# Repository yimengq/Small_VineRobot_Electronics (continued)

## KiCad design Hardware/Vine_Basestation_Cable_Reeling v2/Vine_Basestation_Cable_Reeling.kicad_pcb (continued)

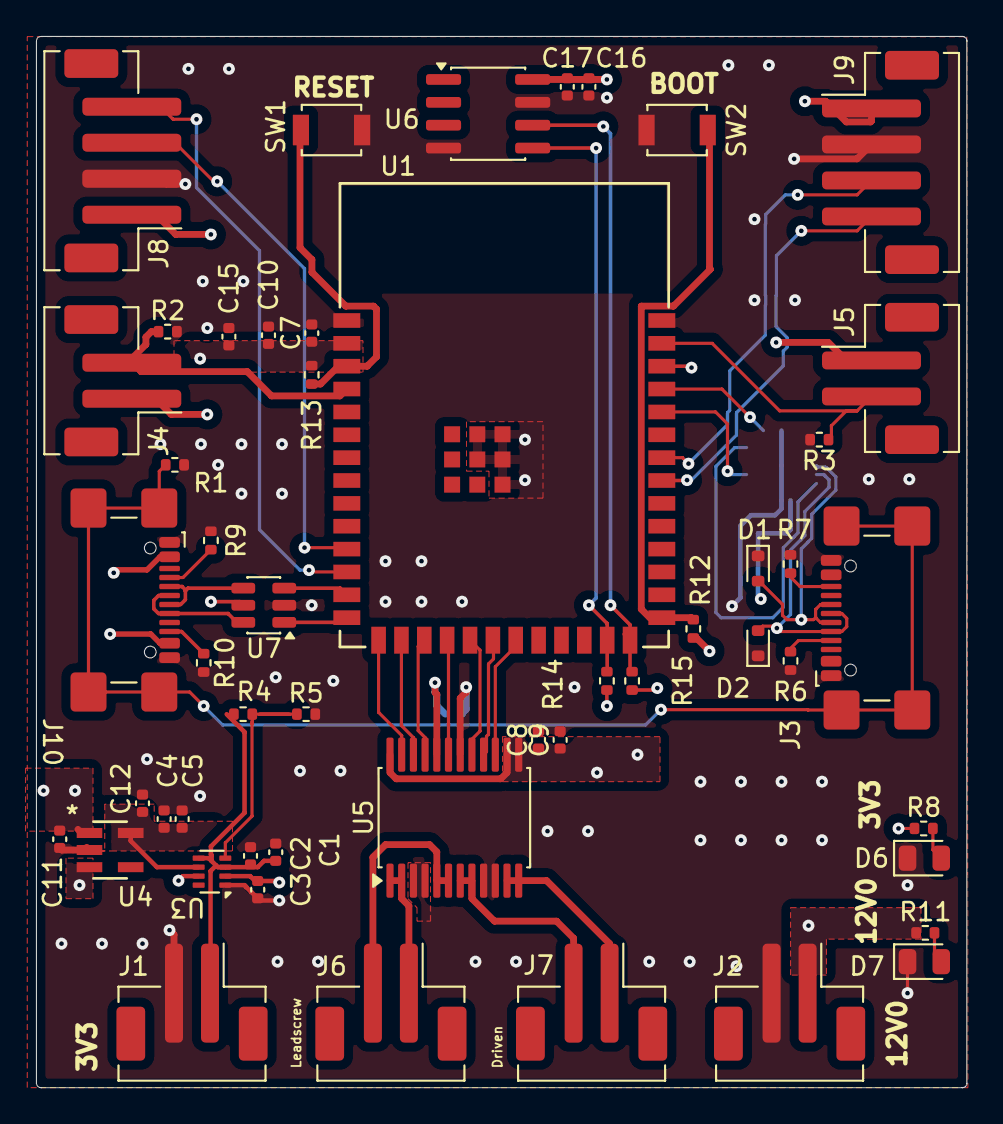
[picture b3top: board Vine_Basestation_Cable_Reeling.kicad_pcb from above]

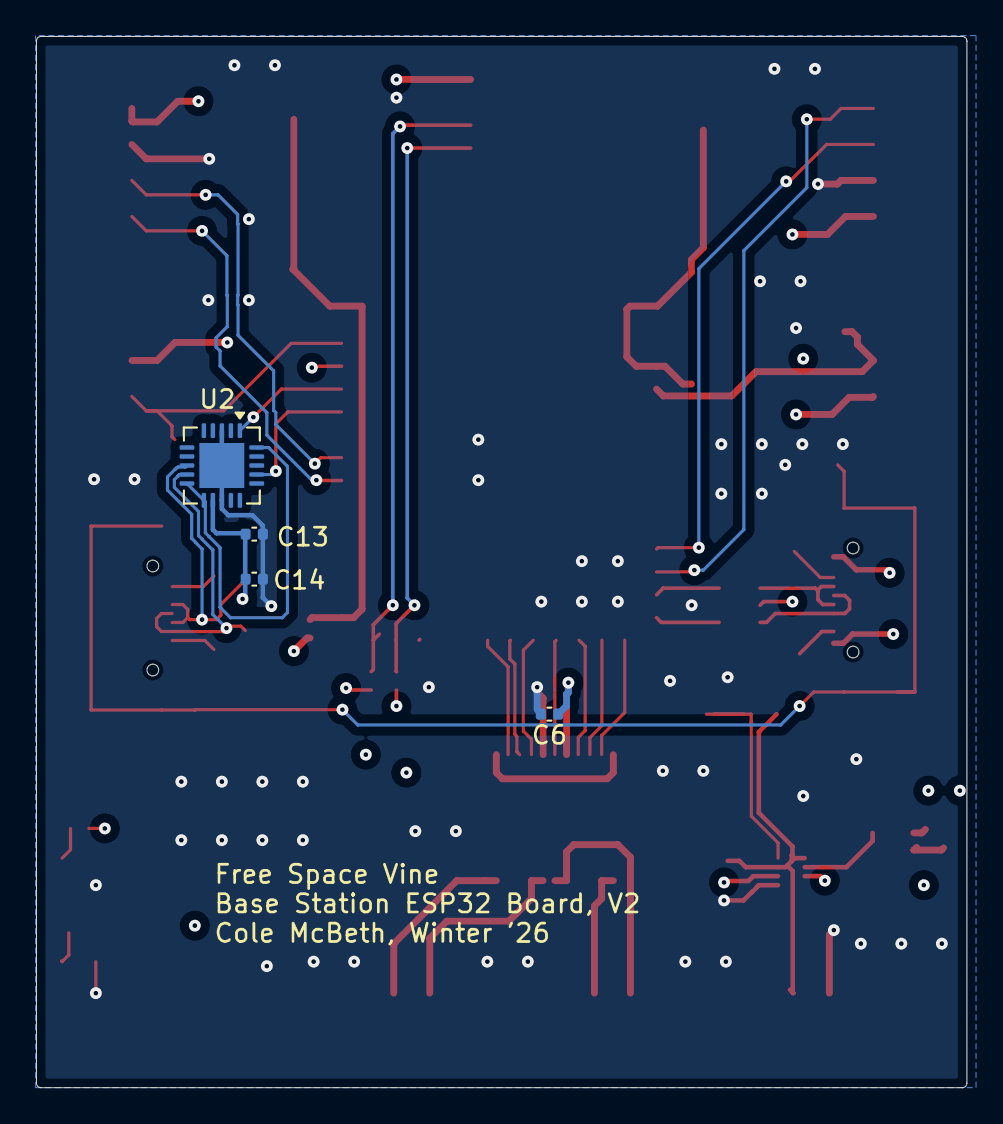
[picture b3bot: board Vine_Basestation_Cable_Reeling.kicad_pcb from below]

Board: 4 copper layers, 51.7 x 58.4 mm, 55 parts (4 on the bottom side), 44 nets.

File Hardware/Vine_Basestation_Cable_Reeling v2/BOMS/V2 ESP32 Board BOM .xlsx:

JLCPCB BOM Tool - BOM Matching
BOM name：ESP32 Board BOM - Vine_Basestation_Cable_Reeli-JLCPCB Assembly Order.x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 |  | Download Time：2025-10-29 07:45:15
PCB Assembled Qty：5 |  | Est. Total Price：39.0998
Designator | Comment | Footprint | JLCPCB Part #
C1,C5,C9,C14, C17 | 4.7u | Capacitor_SMD:C_0402_1005Metric | C23733
C2,C4,C7,C8,C11,C6,C13, C16 | 0.1u | Capacitor_SMD:C_0402_1005Metric | C1581
C3,C12,C15 | 1u | Capacitor_SMD:C_0402_1005Metric | C14445
C10 | 10u | Capacitor_SMD:C_0402_1005Metric | C15525
D1,D2,D3,D4 | D_TVS | Diode_SMD:D_SOD-523 | C20345394
D6,D7 | LED | LED_SMD:LED_0805_2012Metric | C84256
J1,J2,J4,J5,J6,J7 | Conn_01x02_Pin | Connector_JST:JST_PH_B2B-PH-SM4-TB_1x02-1MP_P2.00mm_Vertical | C265003
J3,J10 | USB_C_Receptacle_USB2.0_14P | Connector_USB:USB_C_Receptacle_GCT_USB4110 | C5143397
J8,J9 | Conn_01x04 | Connector_JST:JST_PH_B4B-PH-SM4-TB_1x04-1MP_P2.00mm_Vertical | C160354
J11 | Conn_02x12_Odd_Even | Connector_PinSocket_1.00mm:PinSocket_2x12_P1.00mm_Vertical_SMD | C22427765
R1 | 1M | Resistor_SMD:R_0402_1005Metric | C22369468
R2,R3,R4,R5,R12,R13 | 10k | Resistor_SMD:R_0402_1005Metric | C60489
R6,R7,R9,R10 | 5.1k | Resistor_SMD:R_0402_1005Metric | C105872
R8 | 270.0 | Resistor_SMD:R_0402_1005Metric | C25099
R11 | 2k | Resistor_SMD:R_0402_1005Metric | C4109
R14,R15 | 3.3k | Resistor_SMD:R_0402_1005Metric | C25890
SW1,SW2 | SW_Push | Button_Switch_SMD:SW_SPST_B3U-1000P | C231329
U1 | ESP32-S3-WROOM-1-N16R8 | ESP32-S3-WROOM-1-N16R8:ESP32-S3-WROOM-1_EXP | C2913202
U2 | FT231XQ | Package_DFN_QFN:QFN-20-1EP_4x4mm_P0.5mm_EP2.5x2.5mm | C132159
U3 | TPS2116DRL | Package_TO_SOT_SMD:SOT-583-8 | C3235557
U4 | TCR2EF33_LMCT | TCR2EF33_LM_CT:SOT-25SMV_TOS | C843273
U5 | TB6612FNG | Package_SO:SSOP-24_5.3x8.2mm_P0.65mm | C141517
U7 | USBLC6-2SC6 | Package_TO_SOT_SMD:SOT-23-6 | C7519
U6 | FM24CL16B | Package_SO:SOIC-8_3.9x4.9mm_P1.27mm | C2953561

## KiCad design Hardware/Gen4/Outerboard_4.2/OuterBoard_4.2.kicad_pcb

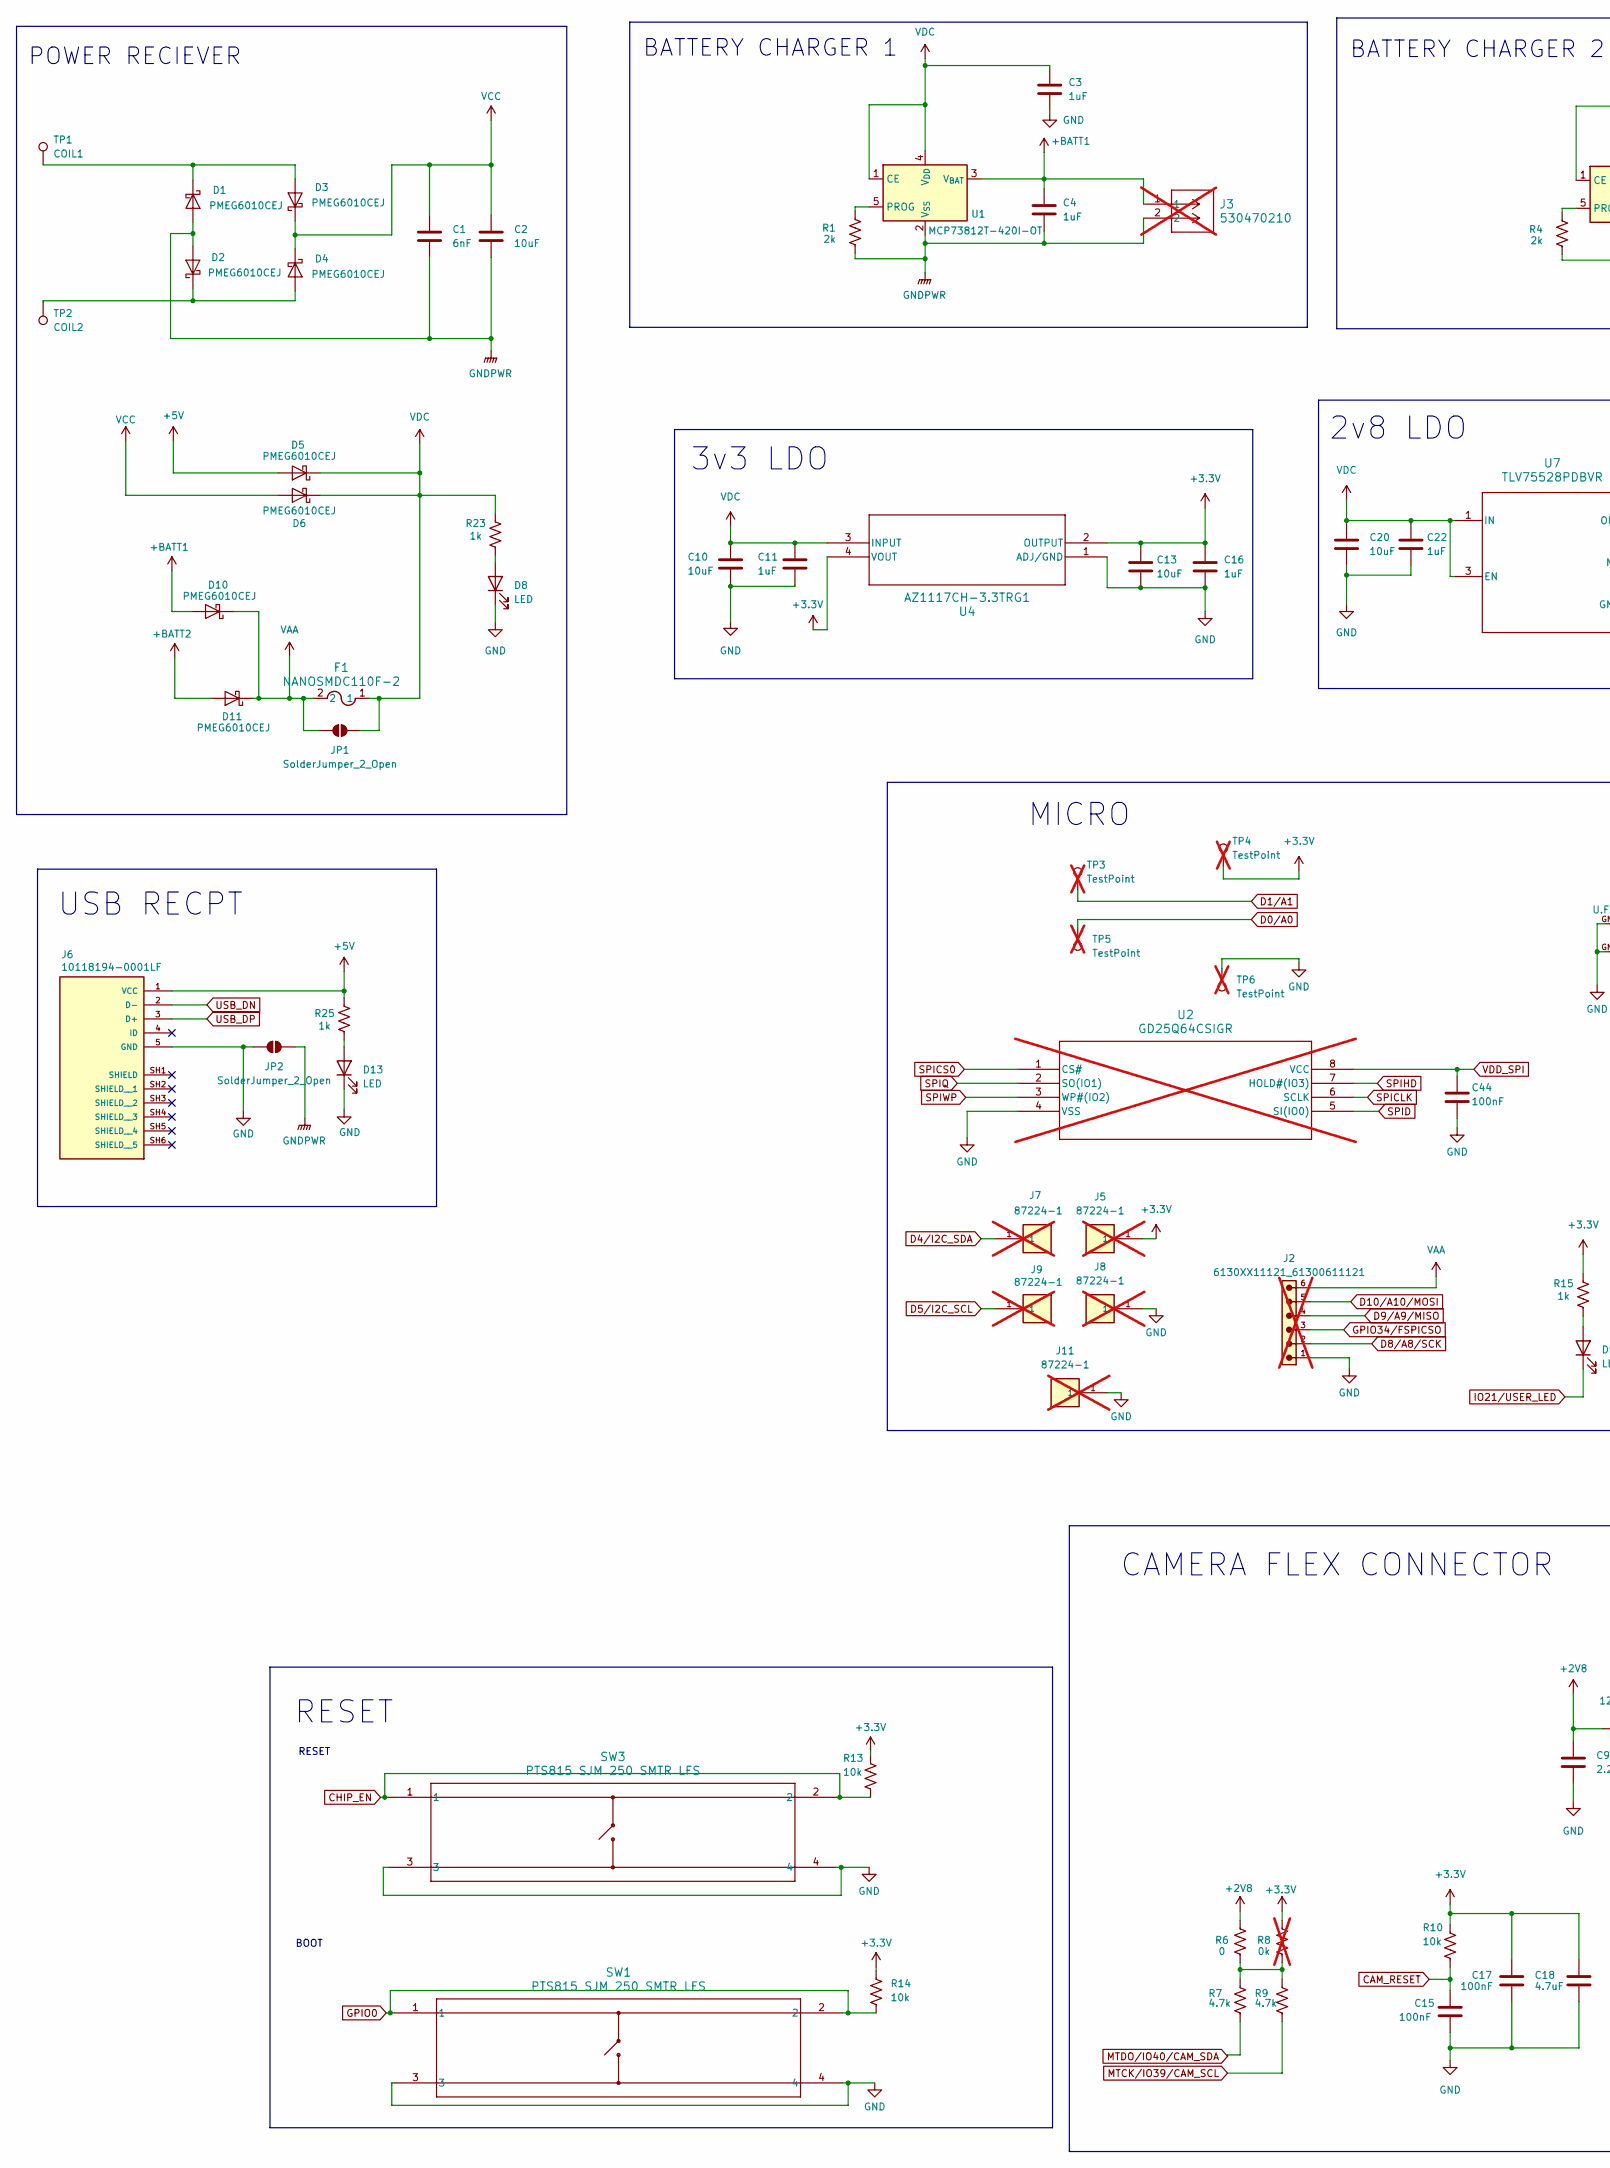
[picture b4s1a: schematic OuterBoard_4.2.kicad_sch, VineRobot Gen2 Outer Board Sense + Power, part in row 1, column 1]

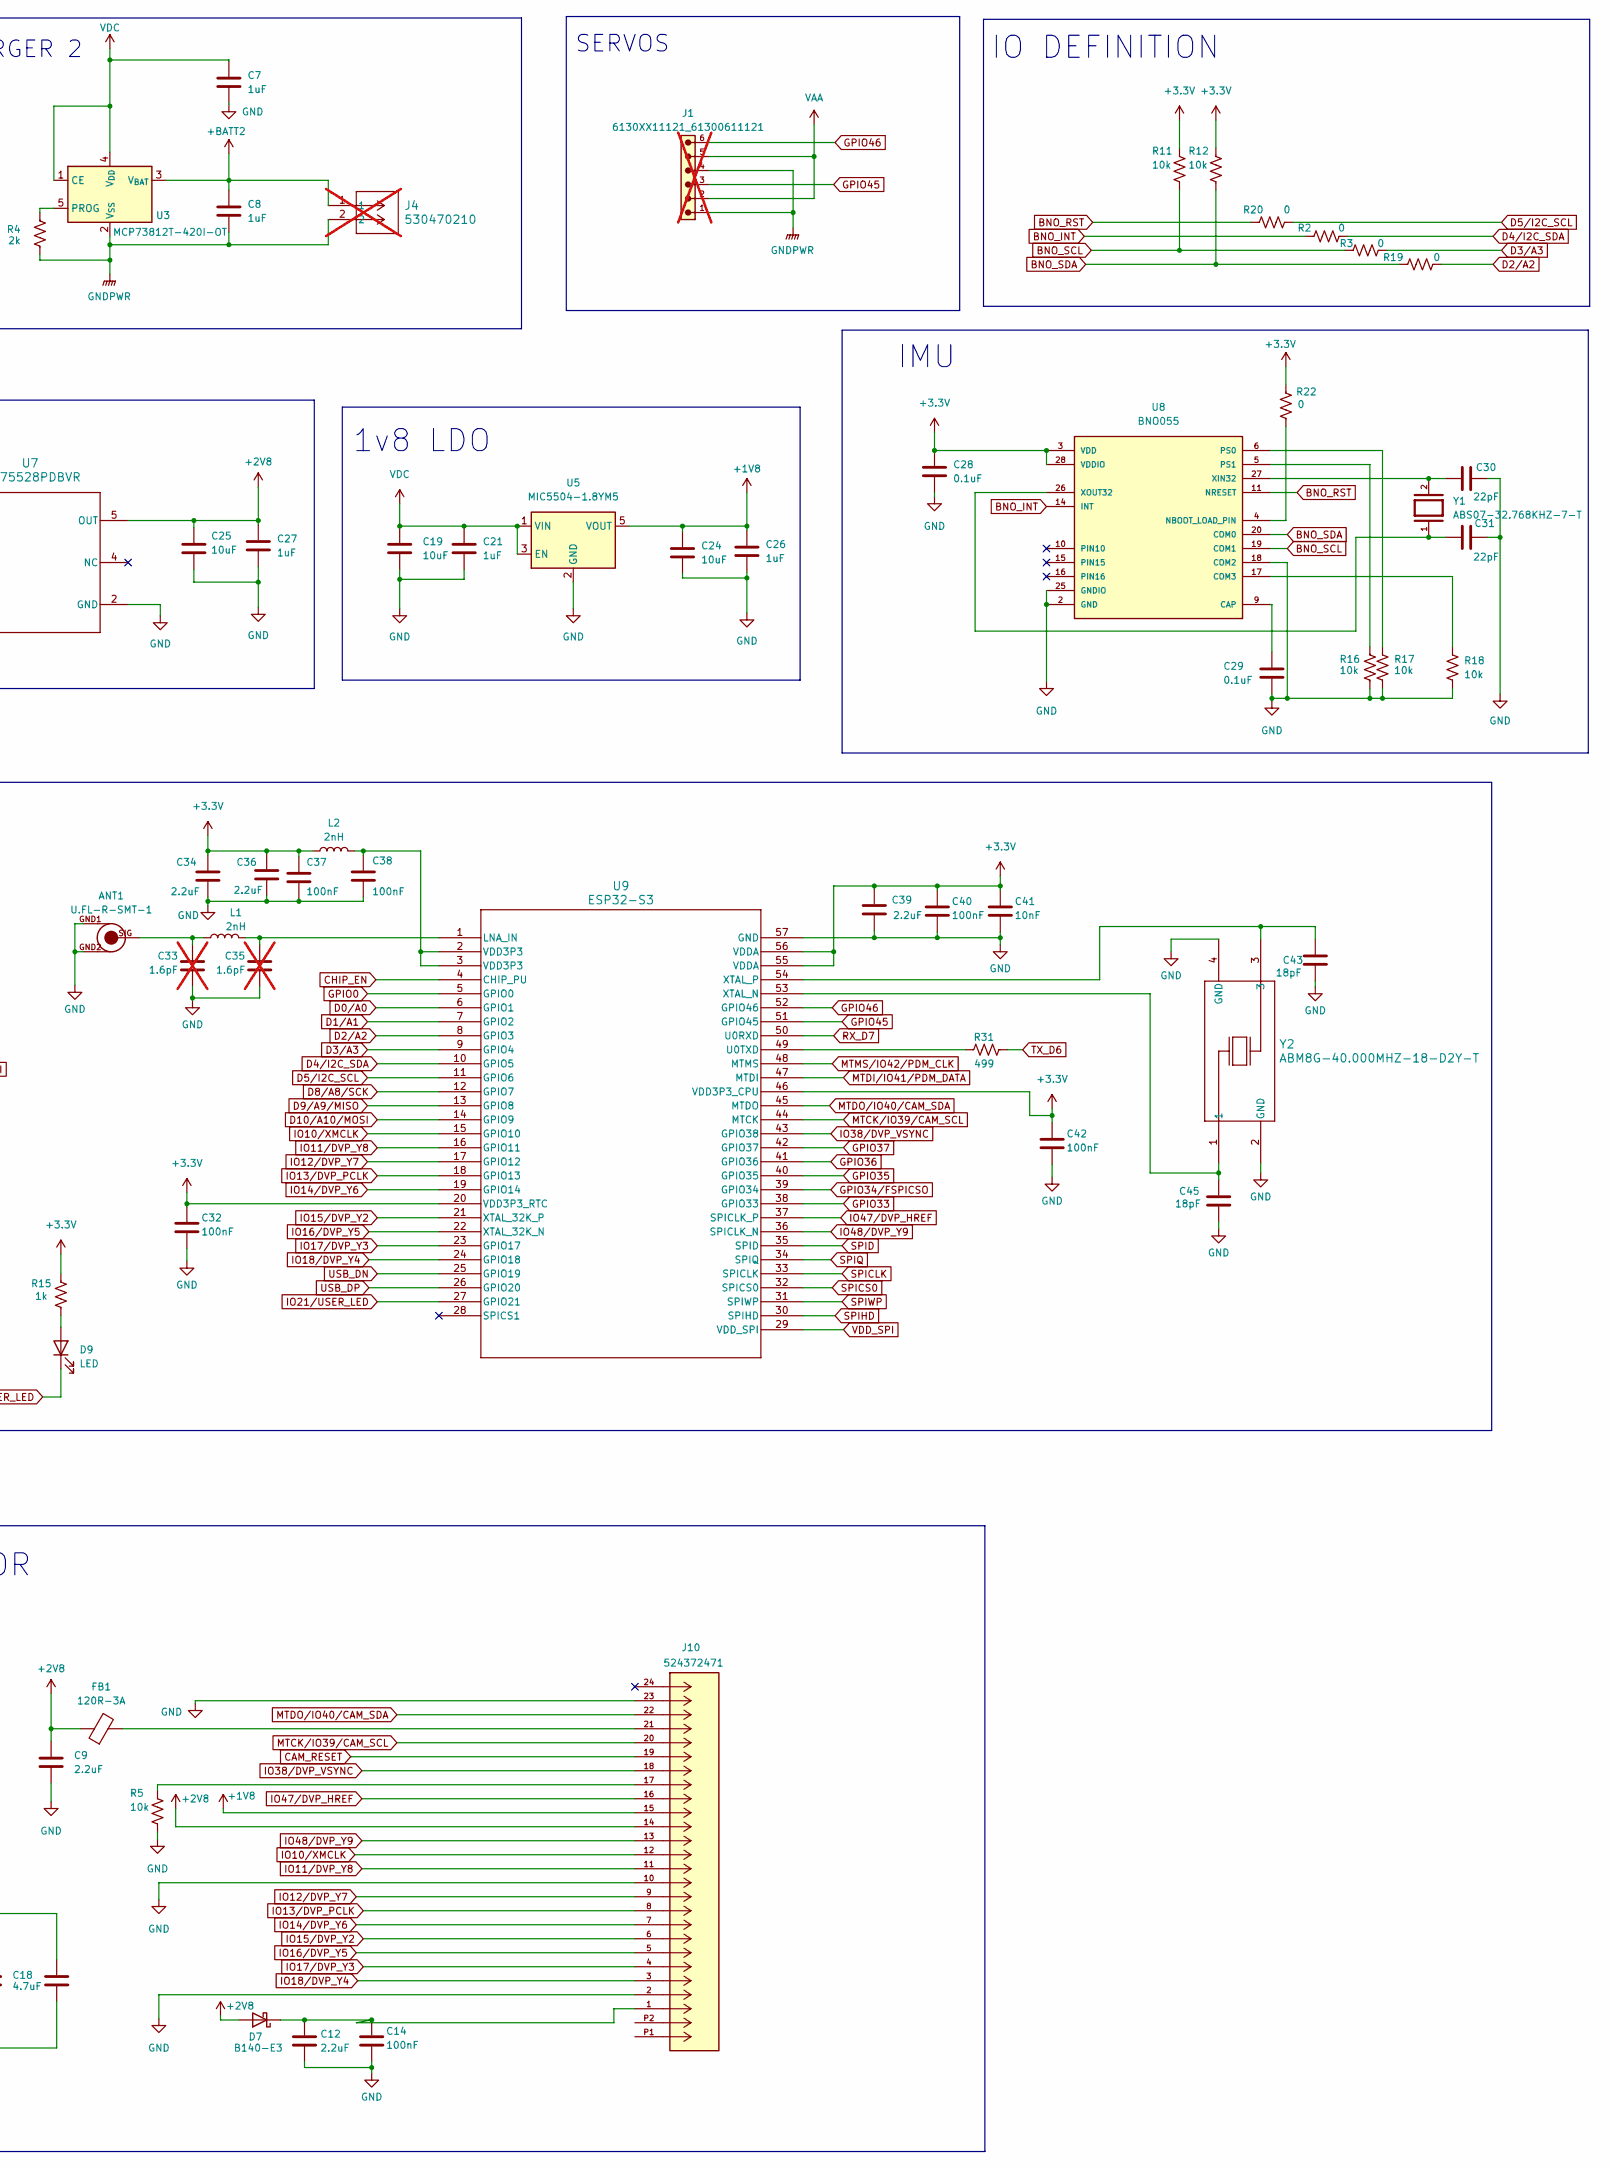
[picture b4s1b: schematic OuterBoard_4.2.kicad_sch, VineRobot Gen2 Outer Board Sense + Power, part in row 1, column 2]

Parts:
ANT1: U.FL-R-SMT-1; Mfr P/N U.FL-R-SMT-1(10)
C1: 6nF; C_0805_2012Metric; Mfr P/N GRM2195C1H562JA01D
C2: 10uF; C_0402_1005Metric; Mfr P/N CL10A106KP8NNNC
C3, C4, C7, C8, C11, C16, C21, C22, C26, C27: 1uF; C_0603_1608Metric; Mfr P/N CC0201MRX5R6BB105
C9, C12, C34, C36, C39: 2.2uF; C_0603_1608Metric; Mfr P/N CL10A225KP8NNNC
C10, C13, C19, C20, C24, C25: 10uF; C_0603_1608Metric; Mfr P/N CL10A106MQ8NNNC
C14, C15, C17, C32, C37, C38, C40, C42, C44: 100nF; C_0603_1608Metric; Mfr P/N CL10B104KA8NNNC
C18: 4.7uF; C_0603_1608Metric; Mfr P/N CL10A475KP8NNNC
C28, C29: 0.1uF; C_0402_1005Metric; Mfr P/N CL05B104KO5NNNC
C30, C31: 22pF; C_0402_1005Metric; Mfr P/N GCM1555C1H220JA16D
C33, C35: 1.6pF; C_0402_1005Metric; Mfr P/N GJM1555C1H1R6WB01D; not fitted
C41: 10nF; C_0402_1005Metric; Mfr P/N 0402B103K500NT
C43, C45: 18pF; C_0201_0603Metric; Mfr P/N 0201CG180J500NT
D1, D2, D3, D4, D5, D6, D10, D11: PMEG6010CEJ; D_SOD-323F; Mfr P/N PMEG6010CEJ
D7: B140-E3; D_SMA; Mfr P/N B140-E3/61T
D8, D9, D13: LED; LED_0603_1608Metric; Mfr P/N KT-0603R
F1: NANOSMDC110F-2; FUS_NANO_TYCO_TYC; Mfr P/N NANOSMDC110F-2
FB1: 120R-3A; C_0805_2012Metric; Mfr P/N BLM21PG121SN1D
J1, J2: 6130XX11121_61300611121; 61300611121; PART-NUMBER 61300611121; not fitted
J3, J4: 530470210; CON_530470210_MOL; Mfr P/N 530470210; not fitted
J5, J7, J8, J9, J11: 87224-1; HDRV1W68P0_1X1_213X213X1036; PARTREV L3; not fitted
J6: 10118194-0001LF; AMPHENOL_10118194-0001LF; PARTREV D
J10: 524372471; CON_524372471_MOL; PARTREV C
JP1, JP2: SolderJumper_2_Open; SolderJumper-2_P1.3mm_Open_Pad1.0x1.5mm
L1: 2nH; L_0201_0603Metric; Mfr P/N LQP03TG2N0B02D
L2: 2nH; L_0402_1005Metric; Mfr P/N LQG15HS2N0B02D
R1, R4: 2k; R_0402_1005Metric; Mfr P/N 0402WGF2001TCE
R2, R3, R6, R19, R20, R22: 0; R_0402_1005Metric; Mfr P/N 0402WGJ0000TCE
R5, R11, R12, R16, R17, R18: 10k; R_0402_1005Metric; Mfr P/N 0402WGJ0103TCE
R7, R9: 4.7k; R_0402_1005Metric; Mfr P/N 0402WGF4701TCE
R8: 0k; R_0805_2012Metric; Mfr P/N RC0201FR-070RL; not fitted
R10: 10k; R_0805_2012Metric; Mfr P/N 0805W8F1002T5E
R13, R14: 10k; C_0402_1005Metric; Mfr P/N 0402WGJ0103TCE
R15, R23, R25: 1k; R_0402_1005Metric; Mfr P/N 0402WGF1001TCE
R31: 499; R_0402_1005Metric; Mfr P/N 0402WGF4990TCE
SW1, SW3: PTS815 SJM 250 SMTR LFS; SW4_PTS815 SJM 250 SMTR LFS_CNK; Mfr P/N PTS815SJG250SMTRLFS
TP1: COIL1; TestPoint_THTPad_2.0x2.0mm_Drill1.0mm
TP2: COIL2; TestPoint_THTPad_2.0x2.0mm_Drill1.0mm
TP3, TP4, TP5, TP6: TestPoint; PinHeader_1x01_P1.00mm_Vertical; not fitted
U1, U3: MCP73812T-420I-OT; SOT-23-5; Mfr P/N MCP73812T-420I/OT
U2: GD25Q64CSIGR; SOP8_208MIL_GDV; not fitted
U4: AZ1117CH-3.3TRG1; SOT-223_DIO; Mfr P/N AZ1117CH-3.3TRG1
U5: MIC5504-1.8YM5; SOT-23-5; Mfr P/N MIC5504-1.8YM5-TR
U7: TLV75528PDBVR; DBV0005A_N; Mfr P/N TLV75528PDBVR
U8: BNO055; LGA28R50P4X10_380X520X100; Mfr P/N BNO055
U9: ESP32-S3; QFN-56-1EP_7x7mm_P0.4mm_EP3.2x3.2mm; Mfr P/N ESP32-S3R8
Y1: ABS07-32.768KHZ-7-T; XTAL_ABS07-32.768KHZ-7-T; PARTREV 08.19.15
Y2: ABM8G-40.000MHZ-18-D2Y-T; CRYSTAL_ABM8G_ABR; Mfr P/N ABM8G-40.000MHZ-18-D2Y-T

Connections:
+1V8: C24.1, C26.1, J10.15, U5.5 (VOUT)
+2V8: C9.1, C25.1, C27.1, D7.2 (A), FB1.1, J10.14, R6.2, U7.5 (OUT)
+3.3V: C13.1, C16.1, C17.1, C18.1, C28.1, C32.1, C34.1, C36.1, C37.1, C39.1, C40.1, C41.1, C42.1, J5.1, L2.1, R8.2, R10.1, R11.1, R12.1, R13.1, R14.1, R15.2, R22.1, TP4.1, U4.2 (OUTPUT), U4.4 (VOUT), U8.3 (VDD), U8.28 (VDDIO), U9.20 (VDD3P3_RTC), U9.46 (VDD3P3_CPU), U9.55 (VDDA), U9.56 (VDDA)
+5V: D5.2 (A), J6.1 (VCC), R25.2
+BATT1: C4.1, D10.2 (A), J3.1, U1.3 (V_{BAT})
+BATT2: C8.1, D11.2 (A), J4.1, U3.3 (V_{BAT})
BNO_INT: R2.2, U8.14 (INT)
BNO_RST: R20.2, U8.11 (NRESET)
BNO_SCL: R3.2, R11.2, U8.19 (COM1)
BNO_SDA: R12.2, R19.2, U8.20 (COM0)
CAM_RESET: C15.1, J10.19, R10.2
CHIP_EN: R13.2, SW3.1, SW3.2, U9.4 (CHIP_PU)
D0/A0: TP5.1, U9.6 (GPIO1)
D1/A1: TP3.1, U9.7 (GPIO2)
D2/A2: R19.1, U9.8 (GPIO3)
D3/A3: R3.1, U9.9 (GPIO4)
D4/I2C_SDA: J7.1, R2.1, U9.10 (GPIO5)
D5/I2C_SCL: J9.1, R20.1, U9.11 (GPIO6)
D8/A8/SCK: J2.2, U9.12 (GPIO7)
D9/A9/MISO: J2.4, U9.13 (GPIO8)
D10/A10/MOSI: J2.5, U9.14 (GPIO9)
GND: ANT1.GND1, ANT1.GND2, C3.2, C7.2, C9.2, C10.2, C11.2, C12.2, C13.2, C14.2, C15.2, C16.2, C17.2, C18.2, C19.2, C20.2, C21.2, C22.2, C24.2, C25.2, C26.2, C27.2, C28.2, C29.2, C30.2, C31.2, C32.2, C33.2, C34.2, C35.2, C36.2, C37.2, C38.2, C39.2, C40.2, C41.2, C42.2, C43.2, C44.2, C45.2, D8.1 (K), D13.1 (K), J2.1, J6.5 (GND), J8.1, J10.2, J10.10, J10.23, J11.1, JP2.1 (A), R5.2, R16.2, R17.2, R18.2, SW1.3, SW1.4, SW3.3, SW3.4, TP6.1, U2.4 (VSS), U4.1 (ADJ/GND), U5.2 (GND), U7.2 (GND), U8.2 (GND), U8.18 (COM2), U8.25 (GNDIO), U9.57 (GND), Y2.2 (GND), Y2.4 (GND)
GNDPWR: C1.2, C2.2, C4.2, C8.2, D1.2 (A), D2.2 (A), J1.1, J1.4, J3.2, J4.2, JP2.2 (B), R1.2, R4.2, U1.2 (V_{SS}), U3.2 (V_{SS})
GPIO0: R14.2, SW1.1, SW1.2, U9.5 (GPIO0)
GPIO33: U9.38 (GPIO33)
GPIO34/FSPICSO: J2.3, U9.39 (GPIO34)
GPIO35: U9.40 (GPIO35)
GPIO36: U9.41 (GPIO36)
GPIO37: U9.42 (GPIO37)
GPIO45: J1.3, U9.51 (GPIO45)
GPIO46: J1.6, U9.52 (GPIO46)
IO10/XMCLK: J10.12, U9.15 (GPIO10)
IO11/DVP_Y8: J10.11, U9.16 (GPIO11)
IO12/DVP_Y7: J10.9, U9.17 (GPIO12)
IO13/DVP_PCLK: J10.8, U9.18 (GPIO13)
IO14/DVP_Y6: J10.7, U9.19 (GPIO14)
IO15/DVP_Y2: J10.6, U9.21 (XTAL_32K_P)
IO16/DVP_Y5: J10.5, U9.22 (XTAL_32K_N)
IO17/DVP_Y3: J10.4, U9.23 (GPIO17)
IO18/DVP_Y4: J10.3, U9.24 (GPIO18)
IO21/USER_LED: D9.1 (K), U9.27 (GPIO21)
IO38/DVP_VSYNC: J10.18, U9.43 (GPIO38)
IO47/DVP_HREF: J10.16, U9.37 (SPICLK_P)
IO48/DVP_Y9: J10.13, U9.36 (SPICLK_N)
MTCK/IO39/CAM_SCL: J10.20, R9.2, U9.44 (MTCK)
MTDI/IO41/PDM_DATA: U9.47 (MTDI)
MTDO/IO40/CAM_SDA: J10.22, R7.2, U9.45 (MTDO)
MTMS/IO42/PDM_CLK: U9.48 (MTMS)
unnamed: ANT1.SIG, C33.1, L1.2
unnamed: C38.1, L2.2, U9.2 (VDD3P3), U9.3 (VDD3P3)
unnamed: D1.1 (K), D3.2 (A), TP1.1
unnamed: D2.1 (K), D4.2 (A), TP2.1
unnamed: C12.1, C14.1, D7.1 (K), J10.1
unnamed: D8.2 (A), R23.1
unnamed: D9.2 (A), R15.1
unnamed: D13.2 (A), R25.1
unnamed: FB1.2, J10.21
unnamed: J10.17, R5.1
unnamed: R6.1, R7.1, R8.1, R9.1
unnamed: R1.1, U1.5 (PROG)
unnamed: R4.1, U3.5 (PROG)
unnamed: C29.1, U8.9 (CAP)
unnamed: R18.1, U8.17 (COM3)
unnamed: R22.2, U8.4 (NBOOT_LOAD_PIN)
unnamed: R17.1, U8.6 (PS0)
unnamed: R16.1, U8.5 (PS1)
unnamed: C30.1, U8.27 (XIN32), Y1.2
unnamed: C31.1, U8.26 (XOUT32), Y1.1
unnamed: C35.1, L1.1, U9.1 (LNA_IN)
unnamed: R31.1, U9.49 (U0TXD)
unnamed: C45.1, U9.53 (XTAL_N), Y2.1
unnamed: C43.1, U9.54 (XTAL_P), Y2.3
RX_D7: U9.50 (U0RXD)
SPICLK: U2.6 (SCLK), U9.33 (SPICLK)
SPICS0: U2.1 (CS#), U9.32 (SPICS0)
SPID: U2.5 (SI(IO0)), U9.35 (SPID)
SPIHD: U2.7 (HOLD#(IO3)), U9.30 (SPIHD)
SPIQ: U2.2 (SO(IO1)), U9.34 (SPIQ)
SPIWP: U2.3 (WP#(IO2)), U9.31 (SPIWP)
TX_D6: R31.2
USB_DN: J6.2 (D-), U9.25 (GPIO19)
USB_DP: J6.3 (D+), U9.26 (GPIO20)
VAA: D10.1 (K), D11.1 (K), F1.2, J1.2, J1.5, J2.6, JP1.1 (A)
VCC: C1.1, C2.1, D3.1 (K), D4.1 (K), D6.2 (A)
VDC: C3.1, C7.1, C10.1, C11.1, C19.1, C20.1, C21.1, C22.1, D5.1 (K), D6.1 (K), F1.1, JP1.2 (B), R23.2, U1.1 (CE), U1.4 (V_{DD}), U3.1 (CE), U3.4 (V_{DD}), U4.3 (INPUT), U5.1 (VIN), U5.3 (EN), U7.1 (IN), U7.3 (EN)
VDD_SPI: C44.1, U2.8 (VCC), U9.29 (VDD_SPI)

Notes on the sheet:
CAMERA FLEX CONNECTOR
RESET
IMU
POWER RECIEVER
MICRO
1v8 LDO
USB RECPT
BOOT
SERVOS
BATTERY CHARGER 1
BATTERY CHARGER 2
IO DEFINITION
2v8 LDO
3v3 LDO

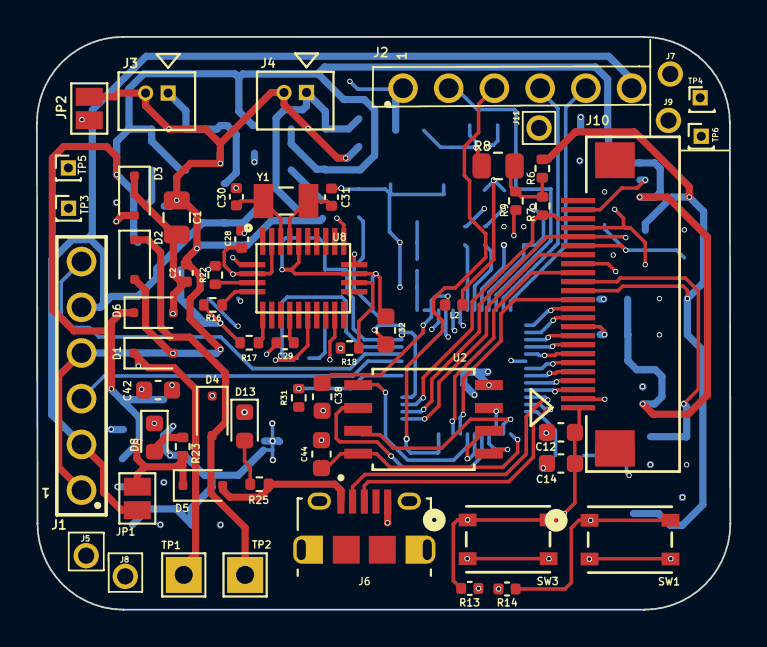
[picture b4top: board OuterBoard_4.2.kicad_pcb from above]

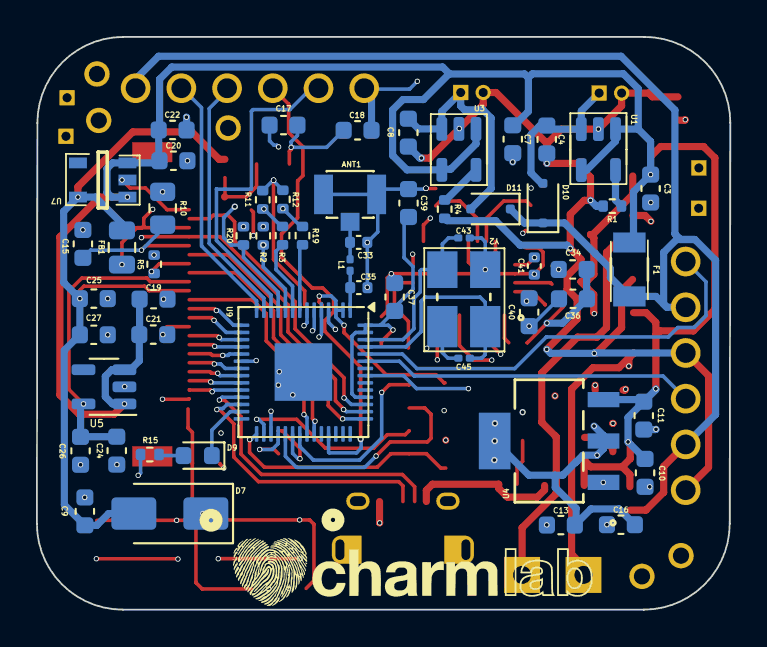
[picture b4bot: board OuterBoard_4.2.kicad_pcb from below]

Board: 6 copper layers, 38.5 x 31.8 mm, 114 parts (56 on the bottom side), 78 nets.

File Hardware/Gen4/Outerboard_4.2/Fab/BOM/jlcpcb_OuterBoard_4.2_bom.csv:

Comment,Designator,Footprint,JLCPCB Part#,,,
U.FL-R-SMT-1,ANT1,U.FL-R-SMT-1:U.FL-R-SMT-1,C88373,,,
6nF,C1,Capacitor_SMD:C_0805_2012Metric,C77067,,,
10uF,"C10,C13,C19,C20,C24,C25",Capacitor_SMD:C_0603_1608Metric,C1691,,,
10uF,C2,Capacitor_SMD:C_0402_1005Metric,C15525,,,
1uF,"C3,C4,C7,C8,C11,C16,C21,C22,C26,C27",Capacitor_SMD:C_0603_1608Metric,C14664,,,
2.2uF,"C9,C12,C34,C36,C39",Capacitor_SMD:C_0603_1608Metric,C1607,,,
100nF,"C14,C15,C17,C32,C37,C38,C40,C42,C44",Capacitor_SMD:C_0603_1608Metric,C1590,,,
4.7uF,C18,Capacitor_SMD:C_0603_1608Metric,C1705,,,
0.1uF,"C28,C29",Capacitor_SMD:C_0402_1005Metric,C1525,,,
22pF,"C30,C31",Capacitor_SMD:C_0402_1005Metric,C126502 ,,,
10nF,C41,Capacitor_SMD:C_0402_1005Metric,C1524,,,
18pF,"C43,C45",Capacitor_SMD:C_0201_0603Metric,C62164,,,
PMEG6010CEJ,"D1,D2,D3,D4,D5,D6,D10,D11",Diode_SMD:D_SOD-323F,C27636122,,,
B140-E3,D7,Diode_SMD:D_SMA,C968568,,,
LED,"D8,D9,D13",LED_SMD:LED_0603_1608Metric,C2286,,,
NANOSMDC110F-2,F1,FUS_NANO_TYCO_TYC,C2649906,,,
120R-3A,FB1,Capacitor_SMD:C_0805_2012Metric,C79382,,,
10118194-0001LF,J6,10118194-0001LF:AMPHENOL_10118194-0001LF,C132563,,,
524372471,J10,524372471:CON_524372471_MOL,C3169564,,,
2nH,L1,Inductor_SMD:L_0201_0603Metric,C86106,,,
2nH,L2,Inductor_SMD:L_0402_1005Metric,C2986275,,,
2k,"R1,R4",Resistor_SMD:R_0402_1005Metric,C4109,,,
0,"R2,R3,R6,R19,R20,R22",Resistor_SMD:R_0402_1005Metric,C21376,,,
10k,"R5,R11,R12,R16,R17,R18",Resistor_SMD:R_0402_1005Metric,C25531,,,
10K,"R13,R14",Capacitor_SMD:C_0402_1005Metric,C25531,,,
10k,R10,Resistor_SMD:R_0805_2012Metric,C17414,,,
4.7k,"R7,R9",Resistor_SMD:R_0402_1005Metric,C25900,,,
1k,"R15,R23,R25",Resistor_SMD:R_0402_1005Metric,C11702,,,
499,R31,Resistor_SMD:R_0402_1005Metric,C4125,,,
PTS815 SJM 250 SMTR LFS,"SW1,SW3",SW4_PTS815 SJM 250 SMTR LFS_CNK,C411883,,,
MCP73812T-420I-OT,"U1,U3",Package_TO_SOT_SMD:SOT-23-5,C144308,,,
GD25Q64CSIGR,U2,SOP8_208MIL_GDV,,,,
AZ1117CH-3.3TRG1,U4,SOT-223_DIO,C92102,,,
MIC5504-1.8YM5,U5,Package_TO_SOT_SMD:SOT-23-5,C626116,,,
TLV75528PDBVR,U7,DBV0005A_N,C723787,,,
BNO055,U8,BNO055:LGA28R50P4X10_380X520X100,C93216,,,
ESP32-S3,U9,Package_DFN_QFN:QFN-56-1EP_7x7mm_P0.4mm_EP3.2x3.2mm,C2913194 ,,,
ABS07-32.768KHZ-7-T,Y1,ABS07-32.768KHZ-7-T:XTAL_ABS07-32.768KHZ-7-T,C276424,,,
ABM8G-40.000MHZ-18-D2Y-T,Y2,CRYSTAL_ABM8G_ABR,C1985459,,,
